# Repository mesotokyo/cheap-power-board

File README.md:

Cheap Power Board - Power Supply Board for Eurorack Modular
===========================================================

Cheap, compact power supply board for Eurorack modular.

 * INPUT: DC 15V
 * OUTPUT: DC +12V, -12V, +5V

This schematic and PCB data uses mst-kicad-lib: https://github.com/mesotokyo/mst-kicad-lib

## BOM

Please check [BOM.txt](BOM.txt).

## Note for assembly

 * U2: The Square pad is for pin 1.
 * It is recommended to use heatsink for U2.
 * The triple pads with rectangle near the center of the board is for U3 (right side of F1). The leftmost pad is for Vout.
   - If you use 7805 type voltage regulator, the leftmost pad is for pin 1.
 * The P3 is jumpmer pin. You can enable 5V output by shorting these pins.
 * The holes on each side can be used to mount the board. The hole spacing matches this PCB terminal [PCB-54L](https://akizukidenshi.com/catalog/g/gC-12218/) and [PCB-54R](https://akizukidenshi.com/catalog/g/gC-12219/).

## LICENSE

CC-BY 4.0 International

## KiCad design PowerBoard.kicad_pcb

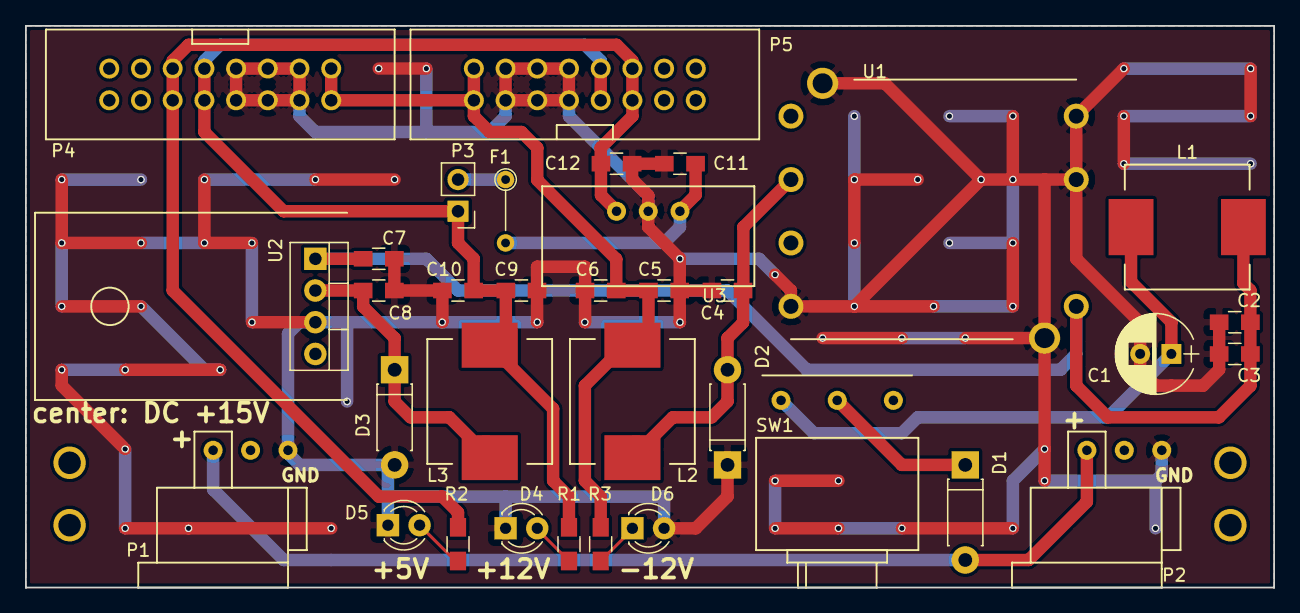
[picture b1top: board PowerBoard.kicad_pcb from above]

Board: 2 copper layers, 100.0 x 45.0 mm, 34 parts (0 on the bottom side), 15 nets.

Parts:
C1: 47u; CP_Radial_D6.3mm_P2.50mm
C2, C5, C9: 10u; C_0805_HandSoldering
C3, C4, C6, C10: 1u; C_0805_HandSoldering
C7, C11: 0.33u; C_0805_HandSoldering
C8: 22u; C_0805_HandSoldering
C12: 0.1u; C_0805_HandSoldering
D1, D2, D3: Schottky; D_DO-41_SOD81_P7.62mm_Horizontal
D4, D5, D6: LED; LED_D3.0mm
F1: PTC0.9A; R_Axial_DIN0204_L3.6mm_D1.6mm_P5.08mm_Vertical
L1, L2, L3: 10u; TAIYO_YUDEN_NR10050
P1, P2: MJ-40
P3: 5V_ON; Pin_Header_Straight_1x02_Pitch2.54mm
P4, P5: CONN_02X08; BOXHEADER-8x2
R1, R3: 4.7k; R_0805_HandSoldering
R2: 2k; R_0805_HandSoldering
SW1: SWITCH_INV; SW-1MS1
U1: CC10-xxxxxF-E; CC6-xxxxxF-E
U2: NJM2396; TO-220-4_Vertical
U3: LM7805CT; ROHM-BP5293

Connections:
+5V: C12.1, P4.11, P4.12, P5.11, P5.12, R2.2, U3.3
+12V: C9.1, C10.2, L3.2, P3.1, P4.9, P4.10, P5.9, P5.10, R1.2
-12V: C5.1, C6.2, L2.2, P4.1, P4.2, P5.1, P5.2, R3.2
GND: C1.2, C2.2, C3.2, C4.2, C5.2, C6.1, C7.2, C8.2, C9.2, C10.1, C11.2, C12.2, D2.1, D3.2, D4.1, D5.1, D6.2, P1.1, P2.1, P4.3, P4.4, P4.5, P4.6, P4.7, P4.8, P5.3, P5.4, P5.5, P5.6, P5.7, P5.8, U1.2, U1.3, U1.7, U2.3, U3.2
unnamed: C1.1, L1.1, SW1.3
unnamed: C4.1, D2.2, L2.1, U1.5
unnamed: C8.1, D3.1, L3.1, U2.2
unnamed: C11.1, F1.2, U3.1
unnamed: D1.1, SW1.2
unnamed: D1.2, P1.3, P2.3
unnamed: D4.2, R1.1
unnamed: D5.2, R2.1
unnamed: D6.1, R3.1
unnamed: F1.1, P3.2
PWR_+: C2.1, C3.1, C7.1, L1.2, U1.1, U2.1

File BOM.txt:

Reference	Value	Footprint
C1	47u	Capacitors_ThroughHole:CP_Radial_D6.3mm_P2.50mm
C2	10u	Capacitors_SMD:C_0805_HandSoldering
C3	1u	Capacitors_SMD:C_0805_HandSoldering
C4	1u	Capacitors_SMD:C_0805_HandSoldering
C5	10u	Capacitors_SMD:C_0805_HandSoldering
C6	1u	Capacitors_SMD:C_0805_HandSoldering
C7	0.33u	Capacitors_SMD:C_0805_HandSoldering
C8	22u	Capacitors_SMD:C_0805_HandSoldering
C9	10u	Capacitors_SMD:C_0805_HandSoldering
C10	1u	Capacitors_SMD:C_0805_HandSoldering
C11	0.33u	Capacitors_SMD:C_0805_HandSoldering
C12	0.1u	Capacitors_SMD:C_0805_HandSoldering
D1	Schottky	Diodes_ThroughHole:D_DO-41_SOD81_P7.62mm_Horizontal
D2	Schottky	Diodes_ThroughHole:D_DO-41_SOD81_P7.62mm_Horizontal
D3	Schottky	Diodes_ThroughHole:D_DO-41_SOD81_P7.62mm_Horizontal
D4	LED	LEDs:LED_D3.0mm
D5	LED	LEDs:LED_D3.0mm
D6	LED	LEDs:LED_D3.0mm
F1	PTC0.9A	Resistors_ThroughHole:R_Axial_DIN0204_L3.6mm_D1.6mm_P5.08mm_Vertical
L1	10u	INDUCTOR:TAIYO_YUDEN_NR10050
L2	10u	INDUCTOR:TAIYO_YUDEN_NR10050
L3	10u	INDUCTOR:TAIYO_YUDEN_NR10050
P1	MJ-40	BOX-HEADER:MJ-40
P2	MJ-40	BOX-HEADER:MJ-40
P3	5V_ON	Pin_Headers:Pin_Header_Straight_1x02_Pitch2.54mm
P4	CONN_02X08	BOX-HEADER:BOXHEADER-8x2
P5	CONN_02X08	BOX-HEADER:BOXHEADER-8x2
R1	4.7k	Resistors_SMD:R_0805_HandSoldering
R2	2k	Resistors_SMD:R_0805_HandSoldering
R3	4.7k	Resistors_SMD:R_0805_HandSoldering
SW1	SWITCH_INV	TOGGLE_SW:SW-1MS1
U1	CC10-1212SF-E	TDK-Lambda-CCx:CC6-1212SF-E
U2	NJM2396	TO_SOT_Packages_THT:TO-220-4_Vertical
U3	LM7805CT	TDK-Lambda-CCx:ROHM-BP5293

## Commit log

2019-01-09 add LICENSE and update README
2019-01-09 resize figures
2023-01-04 Add note for assembly for README.md
2023-01-04 Update documentation
2023-01-04 add panel pdf and eps
